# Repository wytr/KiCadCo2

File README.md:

# KiCadCo2

# ESP 12-F | MH-Z19C | CO2 INDICATOR

Schematic [here](https://github.com/wytr/KiCadCo2/blob/master/schematic_pdf/ESP8266_12F_BASIC.pdf)

Assembly [here](https://github.com/wytr/KiCadCo2/blob/master/Board2Pdf/ESP8266_12F_BASIC-Assembly.pdf)

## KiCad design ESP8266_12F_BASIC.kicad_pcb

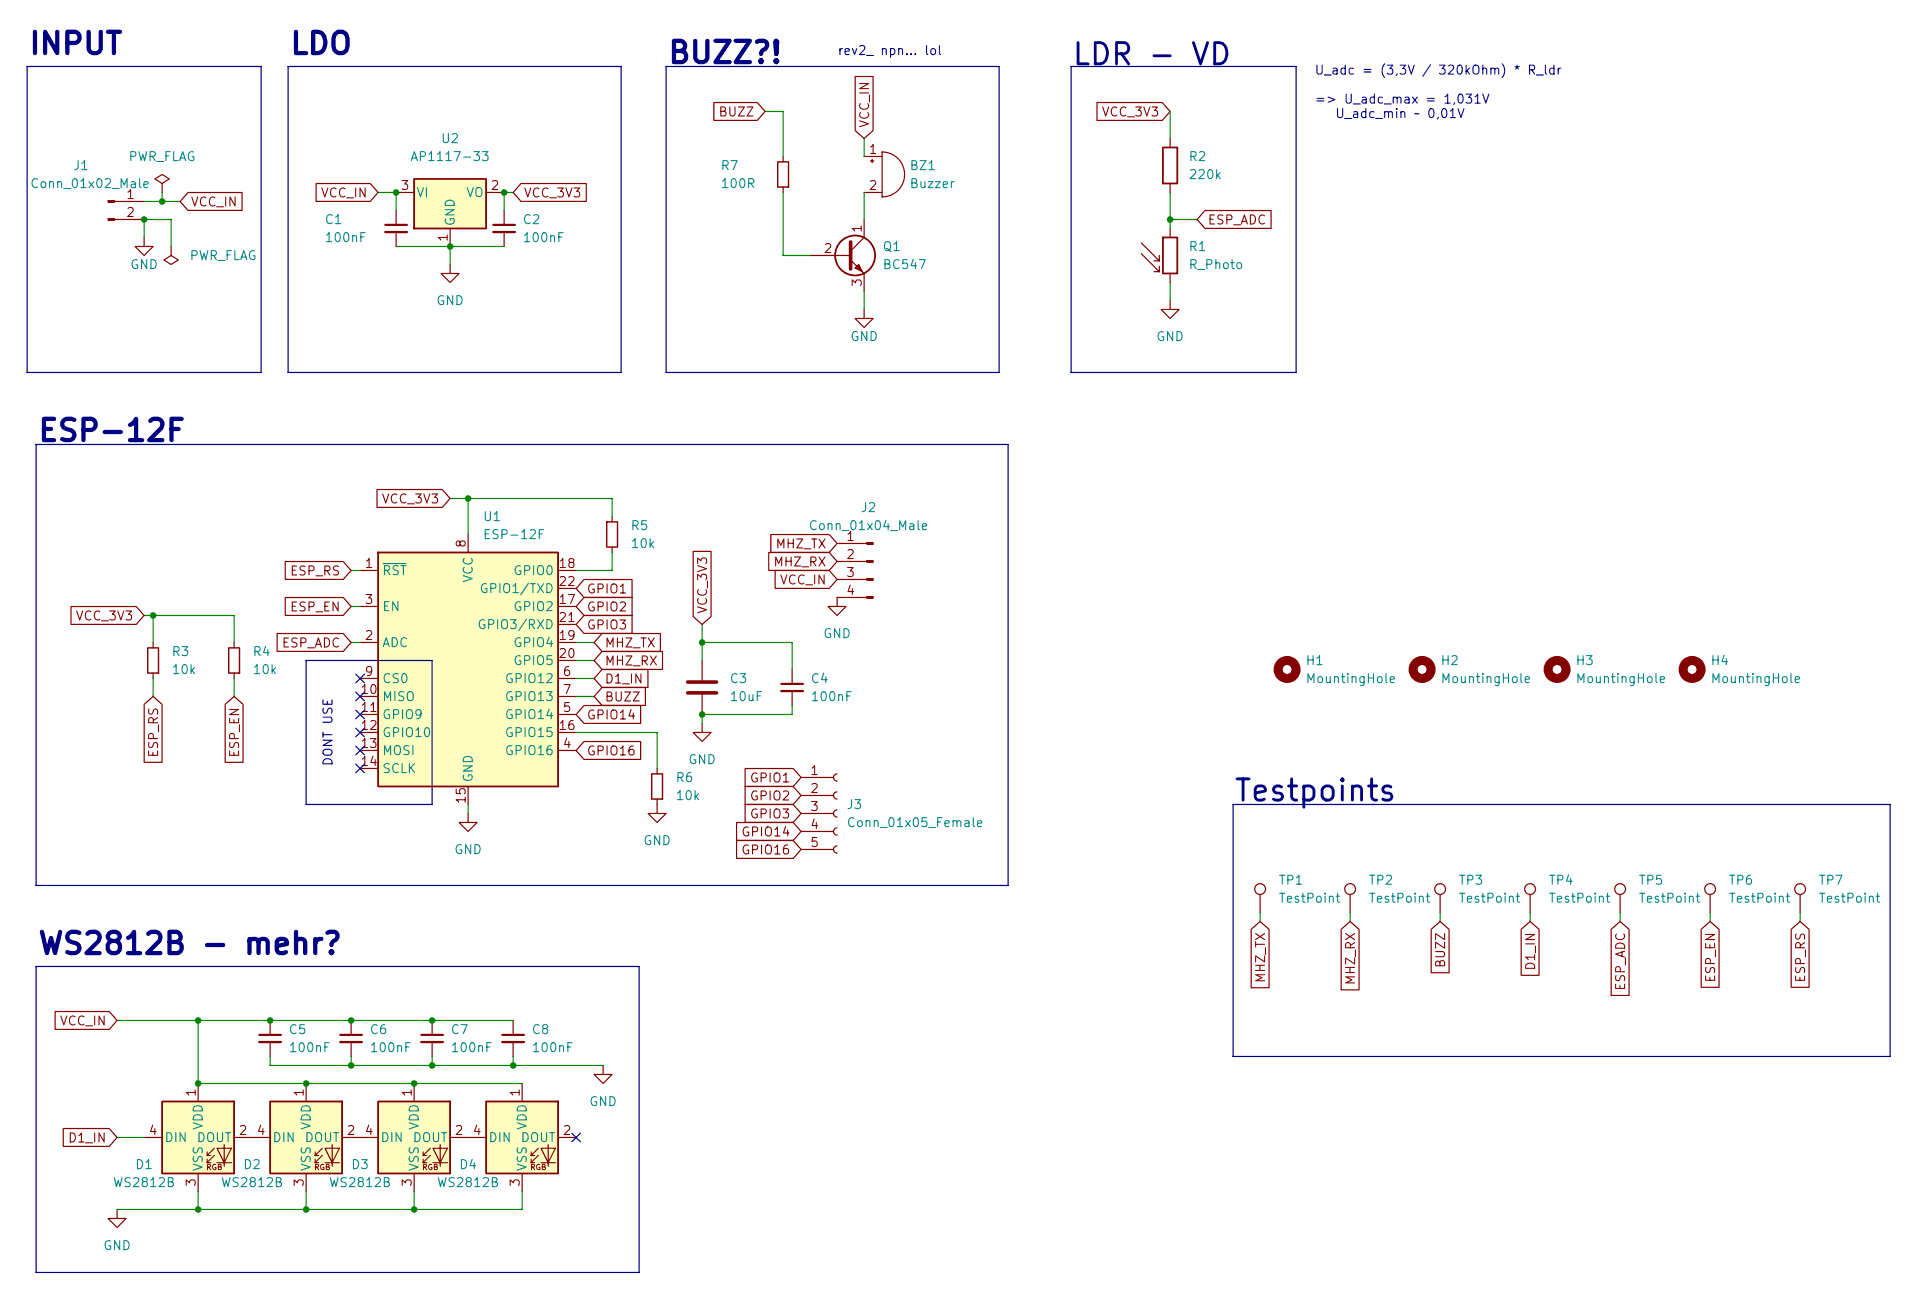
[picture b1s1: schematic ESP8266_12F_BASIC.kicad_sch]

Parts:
BZ1: Buzzer; Buzzer_TDK_PS1240P02BT_D12.2mm_H6.5mm
C1, C2, C5, C6, C7, C8: 100nF; C_0805_2012Metric_Pad1.18x1.45mm_HandSolder
C3: 10uF; CP_Radial_D6.3mm_P2.50mm
C4: 100nF; C_1206_3216Metric_Pad1.33x1.80mm_HandSolder
D1, D2, D3, D4: WS2812B; LED_WS2812B_PLCC4_5.0x5.0mm_P3.2mm
H1, H2, H3, H4: MountingHole; MountingHole_3.2mm_M3
J1: Conn_01x02_Male; JST_XH_B2B-XH-A_1x02_P2.50mm_Vertical
J2: Conn_01x04_Male; JST_XH_B4B-XH-A_1x04_P2.50mm_Vertical
J3: Conn_01x05_Female; PinHeader_1x05_P2.54mm_Vertical
Q1: BC547; TO-92_Inline
R1: R_Photo; R_LDR_5.1x4.3mm_P3.4mm_Vertical
R2: 220k; R_0805_2012Metric_Pad1.20x1.40mm_HandSolder
R3, R4, R5, R6: 10k; R_0805_2012Metric_Pad1.20x1.40mm_HandSolder
R7: 100R; R_0805_2012Metric_Pad1.20x1.40mm_HandSolder
TP1, TP2, TP3, TP4, TP5, TP6, TP7: TestPoint; TestPoint_THTPad_D3.0mm_Drill1.5mm
U1: ESP-12F; ESP-12E
U2: AP1117-33; SOT-223-3_TabPin2

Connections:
BUZZ: R7.2, TP3.1, U1.7 (GPIO13)
D1_IN: D1.4 (DIN), TP4.1, U1.6 (GPIO12)
ESP_ADC: R1.1, R2.2, TP5.1, U1.2 (ADC); also elsewhere on the board
ESP_EN: R4.1, TP6.1, U1.3 (EN)
ESP_RS: R3.1, TP7.1, U1.1 (~RST)
GND: C1.2, C2.2, C3.2, C4.2, C5.2, C6.2, C7.2, C8.2, D1.3 (VSS), D2.3 (VSS), D3.3 (VSS), D4.3 (VSS), J1.2, J2.4, Q1.3 (E), R1.2, R6.1, U1.15 (GND), U2.1 (GND); also elsewhere on the board
GPIO1: J3.1, U1.22 (GPIO1/TXD)
GPIO2: J3.2, U1.17 (GPIO2)
GPIO3: J3.3, U1.21 (GPIO3/RXD)
GPIO14: J3.4, U1.5 (GPIO14)
GPIO16: J3.5, U1.4 (GPIO16)
MHZ_RX: J2.2, TP2.1, U1.20 (GPIO5)
MHZ_TX: J2.1, TP1.1, U1.19 (GPIO4)
unnamed: BZ1.2 (+), Q1.1 (C)
unnamed: D1.2 (DOUT), D2.4 (DIN)
unnamed: D2.2 (DOUT), D3.4 (DIN)
unnamed: D3.2 (DOUT), D4.4 (DIN)
unnamed: R5.2, U1.18 (GPIO0)
unnamed: R6.2, U1.16 (GPIO15)
unnamed: Q1.2 (B), R7.1
VCC_3V3: C2.1, C3.1, C4.1, R2.1, R3.2, R4.2, R5.1, U1.8 (VCC), U2.2 (VO)
VCC_IN: BZ1.1 (-), C1.1, C5.1, C6.1, C7.1, C8.1, D1.1 (VDD), D2.1 (VDD), D3.1 (VDD), D4.1 (VDD), J1.1, J2.3, U2.3 (VI)

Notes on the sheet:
LDR - VD
DONT USE
INPUT
WS2812B - mehr?
rev2_ npn... lol
U_adc = (3,3V / 320kOhm) * R_ldr => U_adc_max = 1,031V U_adc_min ~ 0,01V
LDO
ESP-12F
BUZZ?!
Testpoints

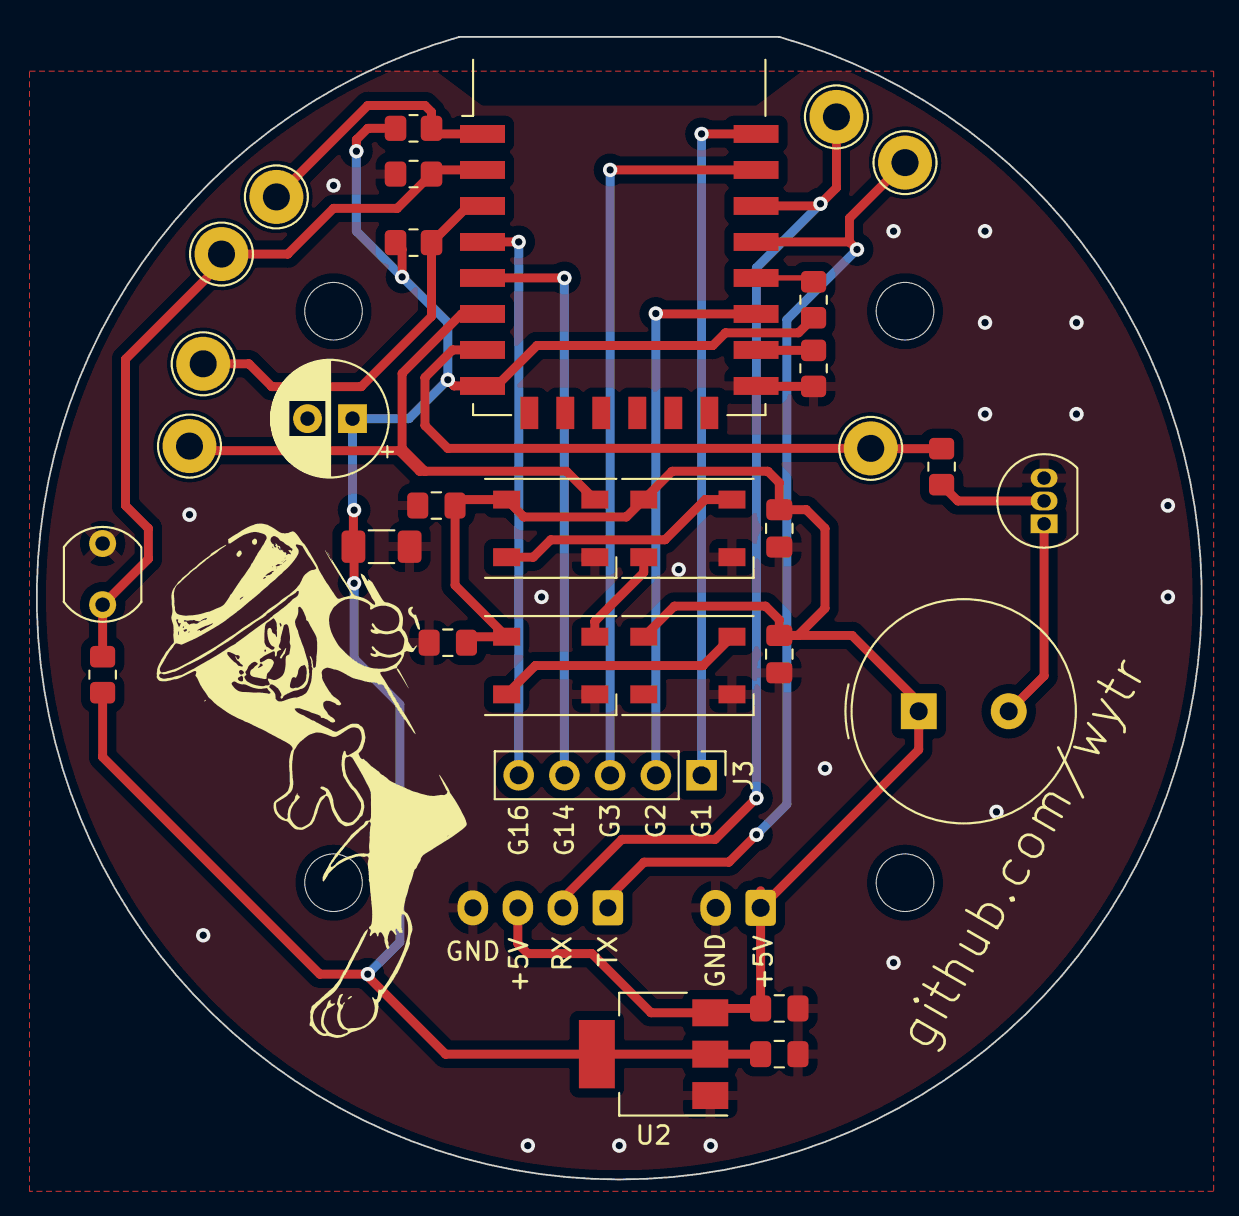
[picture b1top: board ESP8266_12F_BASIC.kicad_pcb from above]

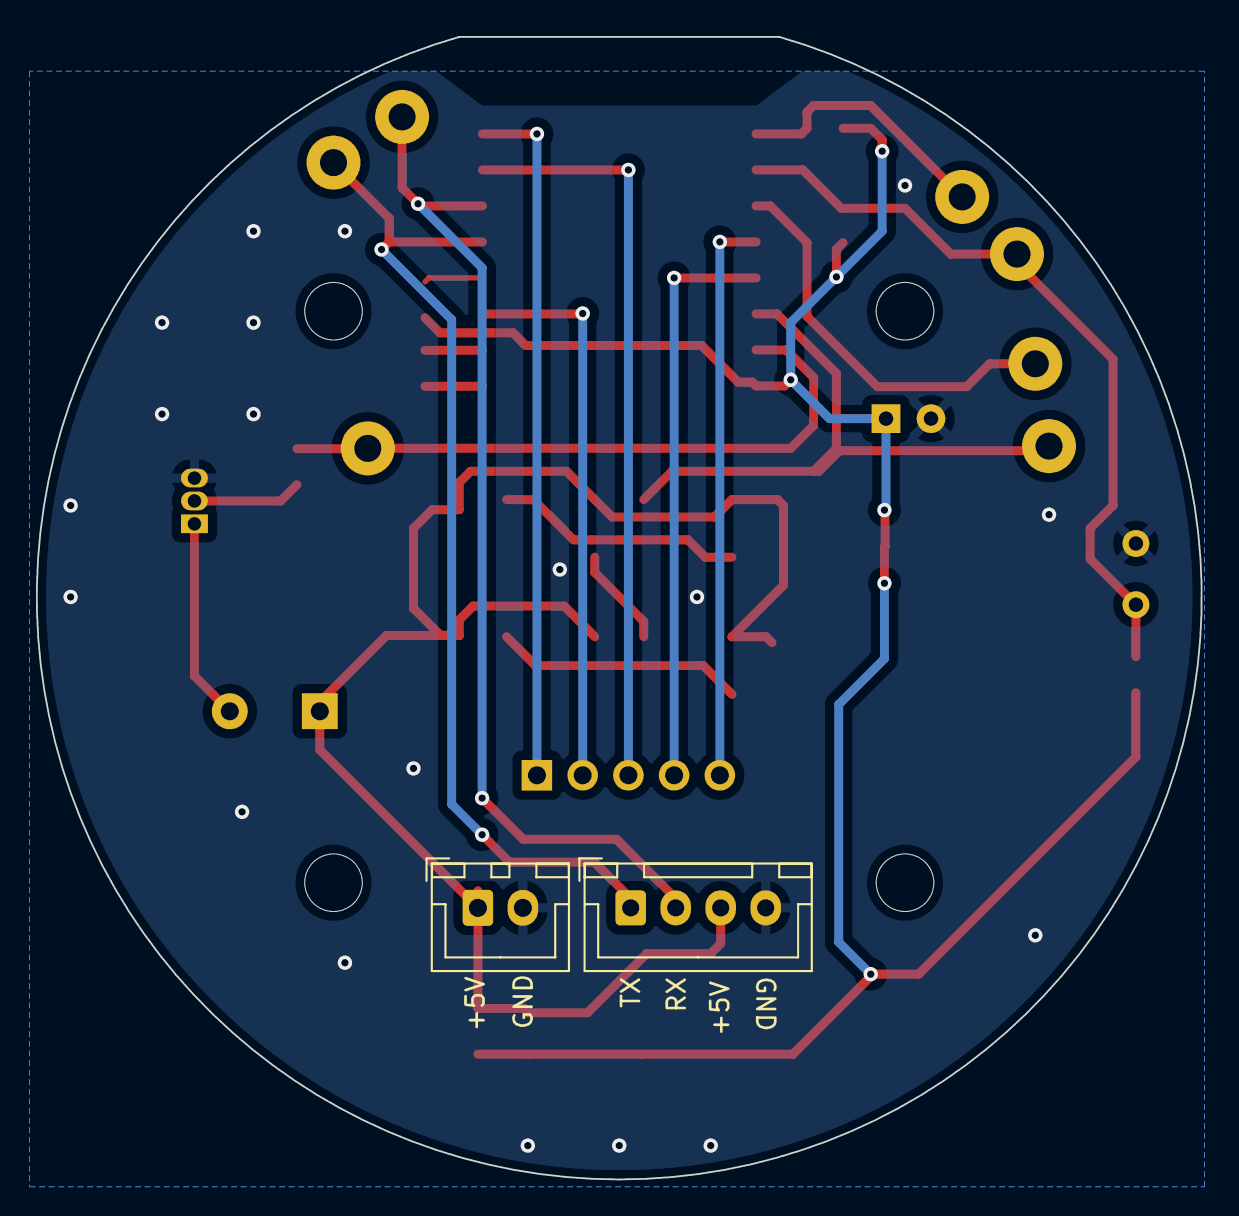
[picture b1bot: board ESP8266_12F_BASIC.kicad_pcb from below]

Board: 2 copper layers, 64.7 x 63.5 mm, 38 parts (2 on the bottom side), 22 nets.

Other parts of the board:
R2#2: 100k; R_0805_2012Metric_Pad1.20x1.40mm_HandSolder

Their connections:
ESP_ADC: R2#2.1; also elsewhere on the board
GND: R2#2.2; also elsewhere on the board

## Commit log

2022-02-03 kicad test
2022-02-03 fixed header position
2022-02-03 added silkscreen for header
2022-02-03 added gerber pdf and pictures
2022-02-03 structure
2022-02-03 added assembly picture
2022-02-03 major fixes
2022-02-03 caps added and move also added new picture
2022-02-03 updated schematic pdf
2022-02-03 updated gerber
2022-02-03 added fabrication files
2022-02-03 fabrication file
2022-02-08 hotfix
2022-02-08 Revert "Update README.md"
    This reverts commit 95bb67409f6286e45f572885bdc5d8b8306181c3.
2022-02-08 reset
2022-02-08 old state no hotfix
2022-02-08 weird shit
2022-02-24 fixed stupid npn error
2022-02-24 rearranged
